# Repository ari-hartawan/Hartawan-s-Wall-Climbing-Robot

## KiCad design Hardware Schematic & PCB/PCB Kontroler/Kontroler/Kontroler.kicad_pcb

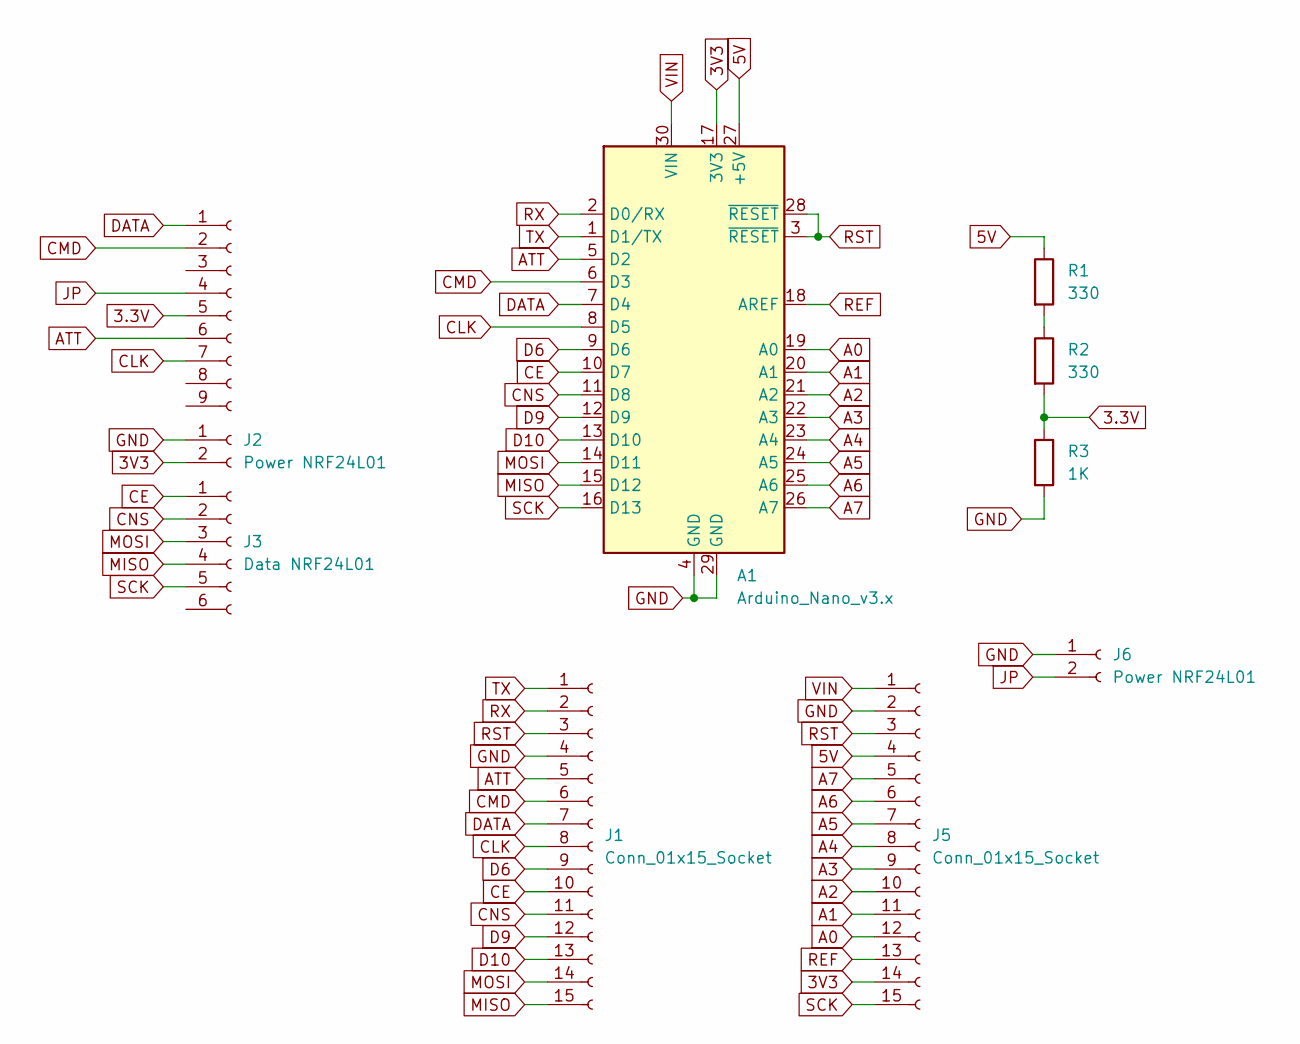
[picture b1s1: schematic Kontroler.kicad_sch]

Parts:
A1: Arduino_Nano_v3.x; Arduino_Nano
J1, J5: Conn_01x15_Socket; PinHeader_1x15_P2.54mm_Vertical
J2: Power NRF24L01; JST_XH_B2B-XH-A_1x02_P2.50mm_Vertical
J3: Data NRF24L01; JST_XH_B6B-XH-A_1x06_P2.50mm_Vertical
J4: Conn_01x09_Socket; JST_VH_B9P-VH-B_1x09_P3.96mm_Vertical
J6: Power NRF24L01; R_Axial_DIN0411_L9.9mm_D3.6mm_P15.24mm_Horizontal
R1, R2: 330; R_Axial_DIN0411_L9.9mm_D3.6mm_P15.24mm_Horizontal
R3: 1K; R_Axial_DIN0411_L9.9mm_D3.6mm_P15.24mm_Horizontal

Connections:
3.3V: J4.5, R2.2, R3.1
3V3: A1.17 (3V3), J2.2, J5.14
5V: A1.27 (+5V), J5.4, R1.1
A0: A1.19 (A0), J5.12
A1: A1.20 (A1), J5.11
A2: A1.21 (A2), J5.10
A3: A1.22 (A3), J5.9
A4: A1.23 (A4), J5.8
A5: A1.24 (A5), J5.7
A6: A1.25 (A6), J5.6
A7: A1.26 (A7), J5.5
ATT: A1.5 (D2), J1.5, J4.6
CE: A1.10 (D7), J1.10, J3.1
CLK: A1.8 (D5), J1.8, J4.7
CMD: A1.6 (D3), J1.6, J4.2
CNS: A1.11 (D8), J1.11, J3.2
D6: A1.9 (D6), J1.9
D9: A1.12 (D9), J1.12
D10: A1.13 (D10), J1.13
DATA: A1.7 (D4), J1.7, J4.1
GND: A1.4 (GND), A1.29 (GND), J1.4, J2.1, J5.2, J6.1, R3.2
JP: J4.4, J6.2
MISO: A1.15 (D12), J1.15, J3.4
MOSI: A1.14 (D11), J1.14, J3.3
unnamed: R1.2, R2.1
REF: A1.18 (AREF), J5.13
RST: A1.3 (~RESET), A1.28 (~RESET), J1.3, J5.3
RX: A1.2 (D0/RX), J1.2
SCK: A1.16 (D13), J3.5, J5.15
TX: A1.1 (D1/TX), J1.1
VIN: A1.30 (VIN), J5.1

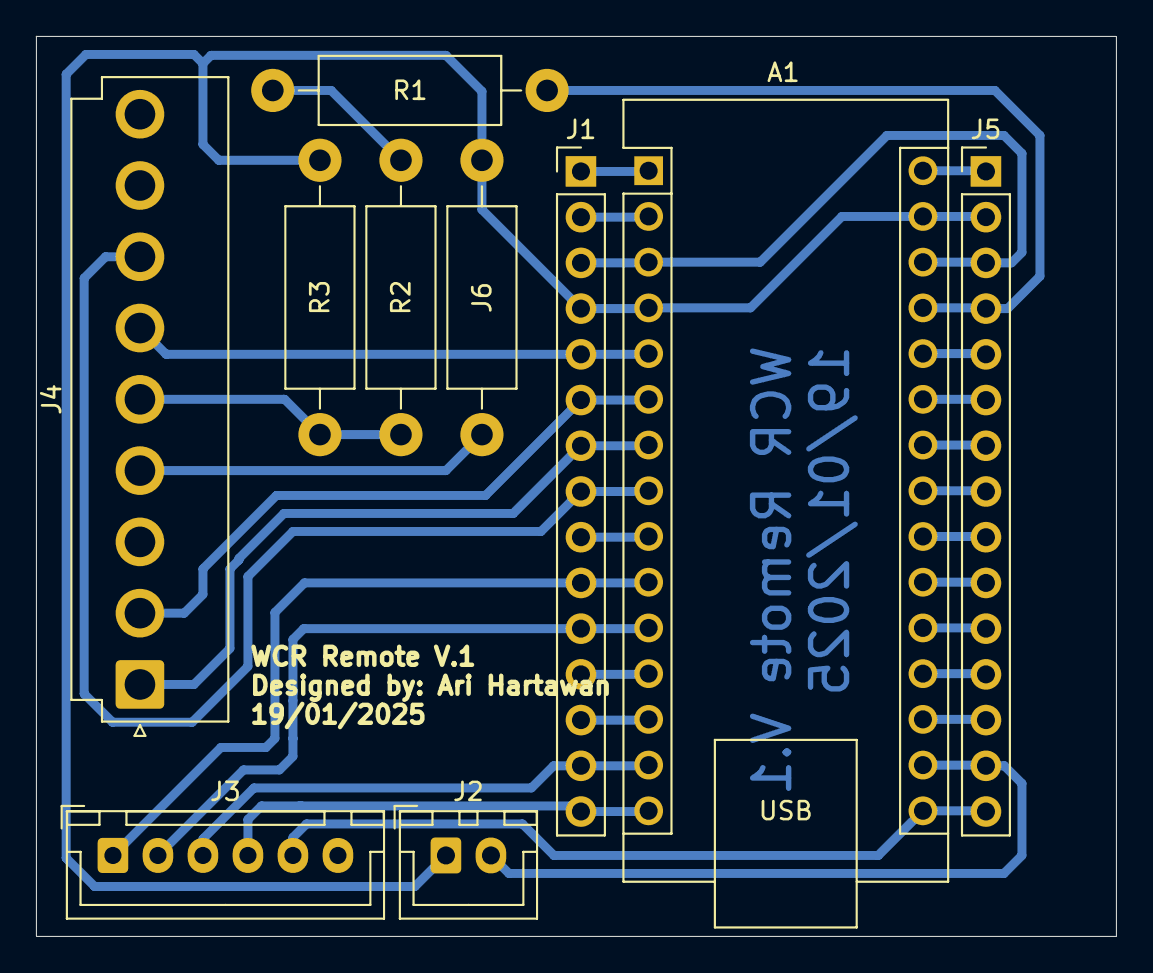
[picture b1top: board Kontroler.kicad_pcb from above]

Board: 2 copper layers, 60.0 x 50.0 mm, 10 parts (0 on the bottom side), 31 nets.

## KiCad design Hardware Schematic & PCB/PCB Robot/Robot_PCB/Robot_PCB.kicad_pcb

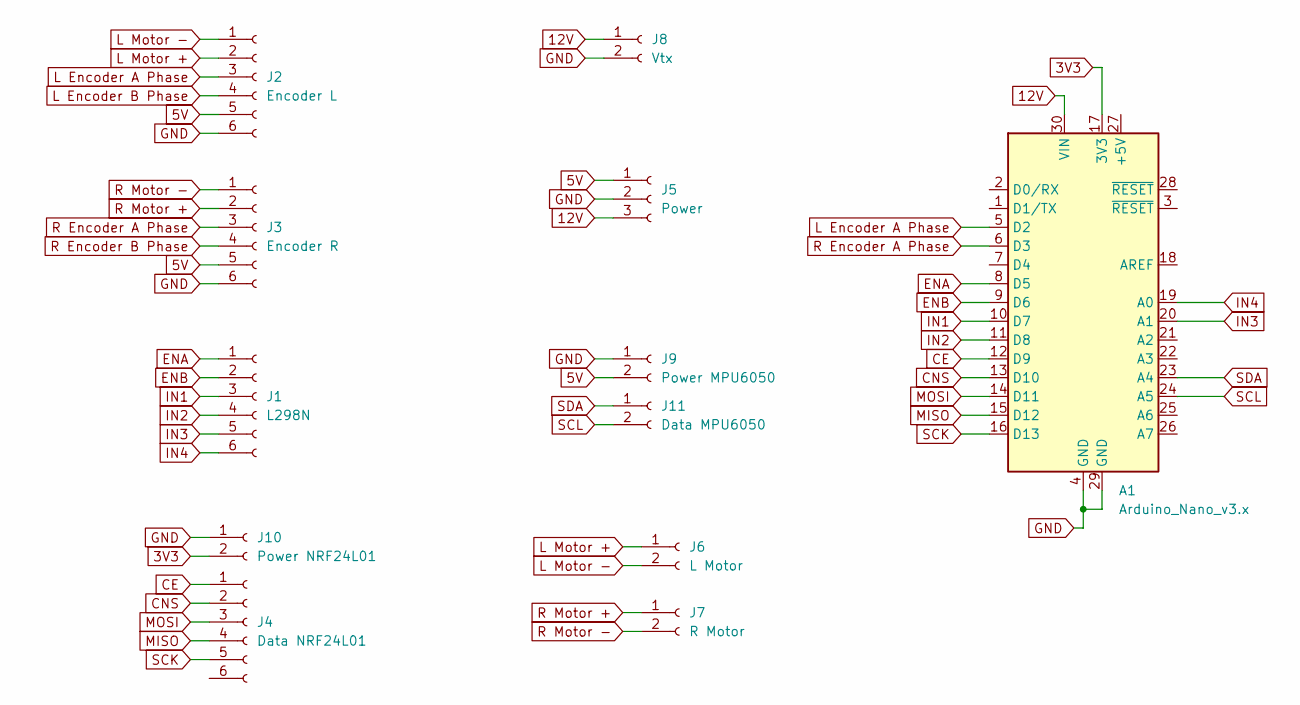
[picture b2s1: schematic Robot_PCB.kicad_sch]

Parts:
A1: Arduino_Nano_v3.x; Arduino_Nano
J1: L298N; JST_XH_B6B-XH-A_1x06_P2.50mm_Vertical
J2: Encoder L; JST_XH_B6B-XH-A_1x06_P2.50mm_Vertical
J3: Encoder R; JST_XH_B6B-XH-A_1x06_P2.50mm_Vertical
J4: Data NRF24L01; JST_XH_B6B-XH-A_1x06_P2.50mm_Vertical
J5: Power; JST_XH_B3B-XH-A_1x03_P2.50mm_Vertical
J6: L Motor; JST_XH_B2B-XH-A_1x02_P2.50mm_Vertical
J7: R Motor; JST_XH_B2B-XH-A_1x02_P2.50mm_Vertical
J8: Vtx; JST_XH_B2B-XH-A_1x02_P2.50mm_Vertical
J9: Power MPU6050; JST_XH_B2B-XH-A_1x02_P2.50mm_Vertical
J10: Power NRF24L01; JST_XH_B2B-XH-A_1x02_P2.50mm_Vertical
J11: Data MPU6050; JST_XH_B2B-XH-A_1x02_P2.50mm_Vertical

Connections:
3V3: A1.17 (3V3), J10.2
5V: J2.5, J3.5, J5.1, J9.2
12V: A1.30 (VIN), J5.3, J8.1
CE: A1.12 (D9), J4.1
CNS: A1.13 (D10), J4.2
ENA: A1.8 (D5), J1.1
ENB: A1.9 (D6), J1.2
GND: A1.4 (GND), A1.29 (GND), J2.6, J3.6, J5.2, J8.2, J9.1, J10.1
IN1: A1.10 (D7), J1.3
IN2: A1.11 (D8), J1.4
IN3: A1.20 (A1), J1.5
IN4: A1.19 (A0), J1.6
L Encoder A Phase: A1.5 (D2), J2.3
L Encoder B Phase: J2.4
L Motor +: J2.2, J6.1
L Motor -: J2.1, J6.2
MISO: A1.15 (D12), J4.4
MOSI: A1.14 (D11), J4.3
R Encoder A Phase: A1.6 (D3), J3.3
R Encoder B Phase: J3.4
R Motor +: J3.2, J7.1
R Motor -: J3.1, J7.2
SCK: A1.16 (D13), J4.5
SCL: A1.24 (A5), J11.2
SDA: A1.23 (A4), J11.1

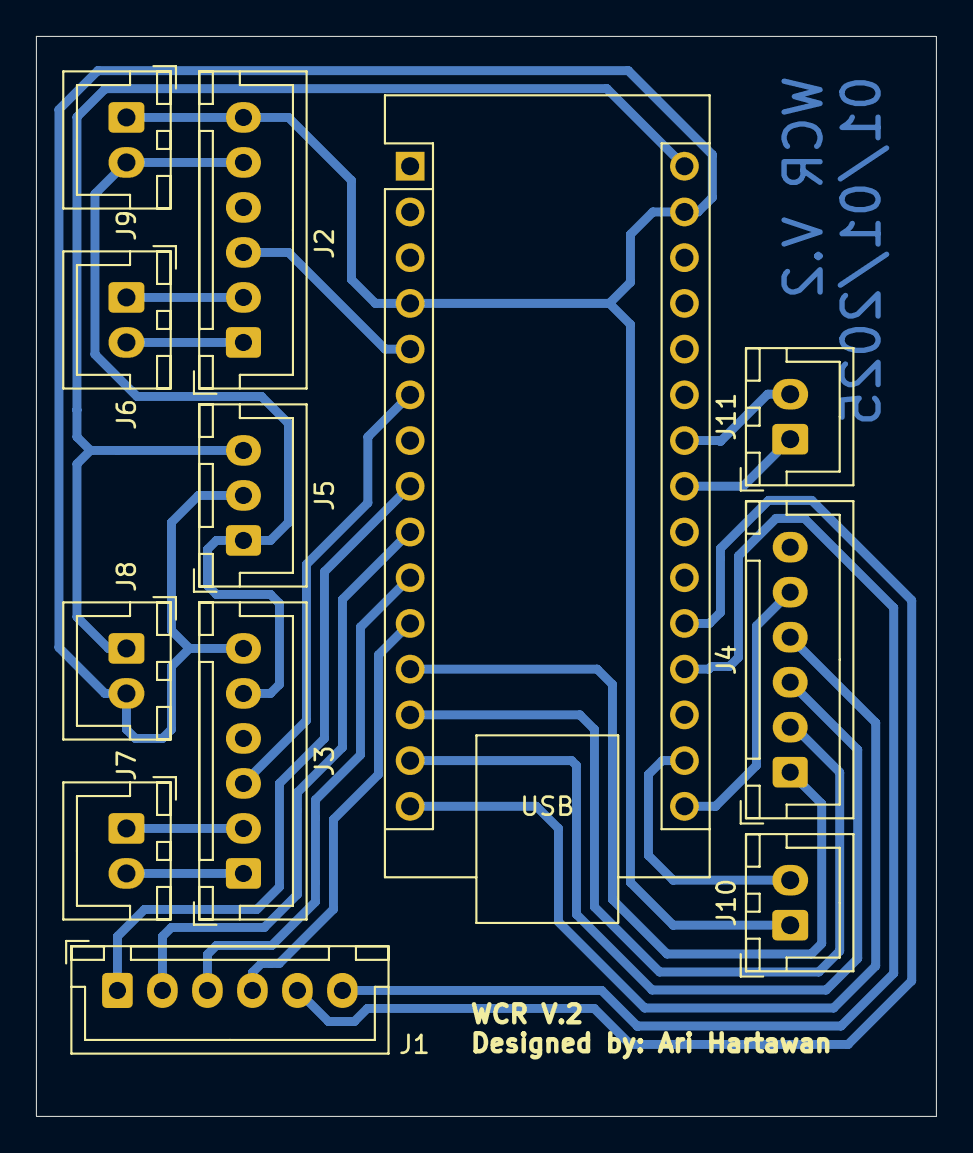
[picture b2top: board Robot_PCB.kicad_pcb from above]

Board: 2 copper layers, 50.0 x 60.0 mm, 12 parts (0 on the bottom side), 23 nets.

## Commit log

2025-06-23 Create Arduino Code
